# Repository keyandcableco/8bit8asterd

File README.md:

# 8b8 — 8-Bit 8asterd firmware

Arduino Leonardo driving three AY-3-8910A chips as a MIDI synth.

## Layout

- `8b8_firmware.ino` — the firmware
- `generate.py` — **single source of truth** for controllable parameters
- `parameters.h` — GENERATED. Do not edit by hand.
- `index.html` — GENERATED. Web Serial control panel (Chrome/Edge only).

## Workflow

Edit `PARAMS` / `PRESETS` in `generate.py`, then:

    python3 generate.py
    arduino-cli compile --fqbn arduino:avr:leonardo .
    arduino-cli upload -p /dev/ttyACM0 --fqbn arduino:avr:leonardo .

`generate.py` hashes the parameter definition into a layout-version byte.
When that byte changes the firmware ignores any saved EEPROM bank and boots
on defaults, so stale saves can never be misread as the new layout.

Open `index.html` directly in Chrome/Edge to control the unit. Close the tab
before flashing or the upload will fail on a busy serial port.

## Constraints

Leonardo (ATmega32u4): 28,672 bytes flash, 2,560 bytes RAM. RAM is the tight
one — keep constant tables in PROGMEM and read them with `pgm_read_*`.

Struct definitions must stay above the first function definition in the
.ino: the Arduino preprocessor inserts generated prototypes there, and a
type declared later breaks the build.

## License

Copyright © 2026 Greg Miller / The Key & Cable Company.

The firmware, browser emulator and tools are licensed under the [GNU General Public License v3.0](LICENSE). You can use, study, share and modify it. If you distribute it or a modified version, you have to make the source available under the same licence.

The hardware design files (the v2 board in `hardware/` on the `v2/rp2040` branch, and front-panel artwork) are licensed under the [CERN Open Hardware Licence Version 2 – Strongly Reciprocal (CERN-OHL-S-2.0)](LICENSE-HARDWARE). You can make, modify, sell and share hardware from them. If you share a modified design, or ship hardware made from one, you have to publish your design files under the same licence.

Source location: <https://github.com/keyandcableco/8bit8asterd>

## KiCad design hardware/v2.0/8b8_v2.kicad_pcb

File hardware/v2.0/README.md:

# 8b8 hardware v2.0

RP2040 board for three YM2149 / AY-3-8910 sound chips, with eight analog
and eight switch inputs on terminal blocks. Everything except the sound chips
and the through-hole connectors is SMD with an LCSC part number, so JLC can
assemble it.

| File | What it is |
|---|---|
| `8b8_v2.kicad_pro`, `.kicad_sch`, `.kicad_pcb` | KiCad 9 project |
| `tools/design.py` | **The netlist, as data.** Every part, footprint, LCSC number and net. |
| `tools/gen_sch.py` | Writes the schematic from `design.py` |
| `tools/gen_pcb.py` | Writes the unrouted board: placement, outline, planes, silkscreen |
| `tools/route.py` | Autoroutes with Freerouting, then adds the copper pours |
| `tools/fixroute.py` | Small A* router for connections the autorouter left open |
| `tools/stitch.py` | Ground vias: beside stranded pads, a 4 mm grid, and inside walled-in pockets |
| `tools/cleanup.py` | Removes dangling track leftovers |
| `tools/check_netlist.py` | Checks that the schematic KiCad reads back matches `design.py` |
| `tools/check_pcb.py` | Checks every pad's net against the schematic, then runs DRC |
| `tools/fab.py` | Writes the JLC package into `fab/` |
| `fab/` | Gerbers (zip), BOM, CPL, and the list of through-hole parts |
| `renders/` | 3D views of the board |

## Status

Checked on the board as committed:

- **Schematic:** KiCad reads back the same 111 nets as `design.py`, with 0 mismatches.
  ERC shows 8 warnings, all one intended thing: the three chips' analog outputs
  are summed, as on v1.0. It's downgraded from error to warning in the project file.
- **Board:** 110 x 90 mm, 4 layers. **DRC: 0 errors, 0 unconnected, 0 schematic
  parity issues.** Every pad carries the right net. 6 cosmetic silkscreen
  warnings remain (a few labels touching vias); JLC clips silk off copper.
- **Stackup:** F.Cu signals, In1 solid GND, In2 signals plus +5V / +3V3 pours,
  B.Cu signals plus GND pour, ~350 stitching vias.
- **Rules:** 0.2 mm tracks, 0.15 mm clearance, 0.25 mm power, 0.6 / 0.3 mm vias.
  All standard JLC 4-layer capability.

### Before ordering

1. **Open it in KiCad and look.** It's autorouted. It's electrically complete
   and DRC-clean, but nobody has eyeballed it yet. Check the RP2040 and crystal
   area in particular, and tidy anything that looks odd.
2. **Check part rotations in JLC's CPL preview.** KiCad and JLC disagree on the
   zero rotation of some footprints (SOT-23, SOIC, the USB-C). JLC shows a
   preview after upload. Rotate any part whose pin 1 sits in the wrong corner.
3. **Through-hole parts** (sockets, terminal blocks) are in `fab/hand_solder.txt`.
   Add them as JLC through-hole assembly, or solder them yourself.
4. **Extended parts:** most ICs are JLC "Extended" library parts, so expect the
   per-part setup fee on top of the parts cost.

## Rebuilding

```bash
cd hardware/v2.0/tools
python3 gen_sch.py && python3 check_netlist.py
/usr/bin/python3 gen_pcb.py                        # needs KiCad's pcbnew module
DISPLAY=:0 /usr/bin/python3 route.py /path/to/freerouting-1.9.0.jar 15
DISPLAY=:0 /usr/bin/python3 route.py /path/to/freerouting-1.9.0.jar 8   # second pass
/usr/bin/python3 fixroute.py && /usr/bin/python3 stitch.py && /usr/bin/python3 stitch.py --islands
/usr/bin/python3 cleanup.py && /usr/bin/python3 check_pcb.py
/usr/bin/python3 fab.py
```

Freerouting 1.9 needs a display; it shows a window while it works. Autorouting
isn't deterministic, so a rebuild won't produce exactly this board. The last
few connections on this one were finished with a rip-up and reroute around
three debounce caps.

`gen_pcb.py` overwrites the board. **Now that it's routed, edit the layout by
hand in KiCad** and use *Update PCB from Schematic* for any circuit change. The
footprints are linked to the schematic symbols, so that works.

## What changed from v1

| | v1.0 (Pro Micro) | v2.0 |
|---|---|---|
| MCU | Pro Micro module on headers (ATmega32U4) | RP2040 on the board, 4 MB QSPI flash, 12 MHz crystal |
| Programming | Arduino bootloader | Hold BOOT, plug in USB, copy a `.uf2`. No programmer needed. |
| Logic to the chips | 5V straight from the 32U4 | Two 74HCT245 buffers (3.3V in, 5V out) |
| Warp Zone bends | A, B, X, Y (data bits DA1, DA0, DA5, DA4) on J3 | **Removed.** The firmware's Warp Zone does this safely. |
| CLK / RESET on J3 | `/SEL` (the half-clock bend) and `/RESET` | **Removed.** Clock Warp does the clock; reset is internal. |
| Inputs | none | 8 analog (74HC4051 to ADC0), 8 switch (74HC165) |
| Power | USB via Pro Micro | USB-C, 0.75 A polyfuse, AP2112K 3.3 V regulator |
| Audio out | 1k / 47n / 1u / 100k network | Same network, same values |
| MIDI in | 6N137, 220R, 1N4148 | Same circuit; output pulled up to 3.3 V |

## RP2040 pin map (for the firmware port)

| GPIO | Signal | Notes |
|---|---|---|
| 0-7 | DA0-DA7 | Data bus via U5. One masked write: `gpio_put_masked(0xFF, b)` |
| 8, 9 | BDIR_A, BC2_A | Chip A control via U6 |
| 10, 11 | BDIR_B, BC2_B | Chip B |
| 12, 13 | BDIR_C, BC2_C | Chip C |
| 14 | /RESET | All three chips. Pulled low until firmware drives it. |
| 15 | LED MIDI | Active high |
| 16 | spare | Test pad (UART0 TX, so a future MIDI out) |
| 17 | MIDI RX | UART0 RX, 31250 baud |
| 18, 19, 20 | MUX S0, S1, S2 | 74HC4051 channel select |
| 21 | CLOCK | GPOUT0. `clk_sys / 125` at 125 MHz gives exactly 1 MHz. Through U6, then 75R, then pin 22 of each chip. |
| 22, 23, 24 | SR /PL, CP, Q7 | 74HC165 |
| 25 | LED STATUS | Active high |
| 26 | MUX Z | ADC0 |
| 27, 28, 29 | spare | Test pads; ADC1-3 |

BC1 is grounded on every chip, the same reduced scheme as v1, so the
register-write sequence is unchanged.

Inside U5 and U6, channel *k* carries bit 7−*k*. That makes the bus run
straight from the RP2040 to the chips without crossing. It doesn't affect the
firmware: GPIO*n* still drives DA*n*.

### Reading the inputs

- **Analog:** set S2..S0 to the channel, wait about 10 µs, then read ADC0.
  Each input has 1k series and 10nF to ground. Pot ends go to the terminal's
  3V3 and GND pins, so the reading is ratiometric.
- **Switches:** pulse /PL low to latch, then clock out 8 bits on CP and read Q7.
  D0 (switch 1) comes out first. Inputs are active low: closed = 0. Each has
  a 10k pull-up and 1k/100nF debounce.

## Open questions

1. **v1.0 C2 is labelled "47uF" but drawn as a 5 mm disc ceramic.** v2.0 uses
   47 nF (3.4 kHz low-pass with the 1k). If your built v1 boards really have
   47 µF there, change it in `design.py`.
2. **v1.0 MIDI terminal labels.** v1's J3 labels the opto-cathode side "MIDI 4"
   and the 220R side "MIDI 5". The MIDI spec has DIN pin 4 on the resistor side,
   so v2.0 labels it that way. The circuit is identical; only the silkscreen
   differs.
3. **/A9, A8 and /SEL are left open, as on v1.0.** The chips pull them to the
   normal state. Tie them explicitly if you prefer.

## License

Copyright © 2026 Greg Miller / The Key & Cable Company.

The v2 hardware design files are licensed under the [CERN Open Hardware Licence Version 2 – Strongly Reciprocal (CERN-OHL-S-2.0)](../../LICENSE-HARDWARE). You can make, modify, sell and share hardware from them. If you share a modified design, or ship hardware made from one, you have to publish your design files under the same licence. The firmware is GPL-3.0 (see [LICENSE](../../LICENSE)).

Source location: <https://github.com/keyandcableco/8bit8asterd>

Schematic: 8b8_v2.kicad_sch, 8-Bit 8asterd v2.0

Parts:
C1, C2, C3: 10uF; C_0603_1608Metric; LCSC C96446
C4, C16, C17: 1uF; C_0402_1005Metric; LCSC C52923
C5: 10uF; C_0603_1608Metric; LCSC C19702
C6, C7, C8, C9, C10, C11, C12, C13, C14, C15, C20, C21, C22, C23, C24, C25, C28, C29, C38, C39, C40, C41, C42, C43, C44, C45, C46: 100nF; C_0402_1005Metric; LCSC C1525
C18, C19: 15pF; C_0402_1005Metric; LCSC C1548
C26: 47nF; C_0402_1005Metric; LCSC C272875
C27: 1uF; C_0603_1608Metric; LCSC C106248
C30, C31, C32, C33, C34, C35, C36, C37: 10nF; C_0402_1005Metric; LCSC C15195
D1: PWR; LED_0603_1608Metric; LCSC C12624
D2: MIDI; LED_0603_1608Metric; LCSC C12624
D3: STATUS; LED_0603_1608Metric; LCSC C2286
D4: 1N4148W; D_SOD-123; LCSC C81598
F1: 0.75A; Fuse_1206_3216Metric; LCSC C70078
H1, H2, H3, H4: M3; MountingHole_3.2mm_M3
J1: USB-C; USB_C_Receptacle_HRO_TYPE-C-31-M-12; LCSC C165948
J2: AUDIO OUT; PhoenixContact_MC_1,5_2-G-3.5_1x02_P3.50mm_Horizontal; LCSC C395830
J3: MIDI IN; PhoenixContact_MC_1,5_2-G-3.5_1x02_P3.50mm_Horizontal; LCSC C395830
J4: ANALOG IN; PhoenixContact_MC_1,5_10-G-3.5_1x10_P3.50mm_Horizontal; LCSC C430562
J5: SWITCH IN; PhoenixContact_MC_1,5_10-G-3.5_1x10_P3.50mm_Horizontal; LCSC C430562
R1, R2: 5.1k; R_0402_1005Metric; LCSC C25905
R3, R4, R5, R8, R9, R19, R23, R24, R25, R26, R27, R28, R29, R30, R31, R33, R35, R37, R39, R41, R43, R45: 1k; R_0402_1005Metric; LCSC C11702
R6, R7: 27; R_0402_1005Metric; LCSC C25156
R10, R11, R12, R13, R14, R15, R16, R17, R20: 100k; R_0402_1005Metric; LCSC C25741
R18: 75; R_0402_1005Metric; LCSC C25133
R21: 220; R_0402_1005Metric; LCSC C25091
R22, R32, R34, R36, R38, R40, R42, R44, R46: 10k; R_0402_1005Metric; LCSC C25744
SW1: BOOT; SW_Push_1P1T_NO_CK_KMR2; LCSC C318884
SW2: RESET; SW_Push_1P1T_NO_CK_KMR2; LCSC C318884
TP_3V3: TP_3V3; TestPoint_Pad_D1.0mm
TP_5V: TP_5V; TestPoint_Pad_D1.0mm
TP_GND: TP_GND; TestPoint_Pad_D1.0mm
TP_GP16: TP_GP16; TestPoint_Pad_D1.0mm
TP_GP27: TP_GP27; TestPoint_Pad_D1.0mm
TP_GP28: TP_GP28; TestPoint_Pad_D1.0mm
TP_GP29: TP_GP29; TestPoint_Pad_D1.0mm
TP_SWCLK: TP_SWCLK; TestPoint_Pad_D1.0mm
TP_SWD: TP_SWD; TestPoint_Pad_D1.0mm
U1: AP2112K-3.3; SOT-23-5; LCSC C51118
U2: RP2040; QFN-56-1EP_7x7mm_P0.4mm_EP3.2x3.2mm; LCSC C2040
U3: W25Q32JVSSIQ; SOIC-8_5.3x5.3mm_P1.27mm; LCSC C179173
U4: USBLC6-2SC6; SOT-23-6; LCSC C7519
U5, U6: 74HCT245; SOIC-20W_7.5x12.8mm_P1.27mm; LCSC C5979
U7, U8, U9: YM2149 / AY-3-8910; DIP-40_W15.24mm_Socket; LCSC C2332
U10: 6N137S; SMDIP-8_W9.53mm; LCSC C16496
U11: 74HC4051; SOIC-16_3.9x9.9mm_P1.27mm; LCSC C9386
U12: 74HC165; SOIC-16_3.9x9.9mm_P1.27mm; LCSC C5613
Y1: 12MHz; Crystal_SMD_3225-4Pin_3.2x2.5mm; LCSC C9002

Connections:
+1V1: C14.1, C15.1, C17.1, U2.23 (DVDD), U2.45 (VREG_VOUT), U2.50 (DVDD)
+3V3: C5.1, C6.1, C7.1, C8.1, C9.1, C10.1, C11.1, C12.1, C13.1, C16.1, C20.1, C29.1, C38.1, J4.9, J5.10, R22.2, R32.2, R34.2, R36.2, R38.2, R40.2, R42.2, R44.2, R46.2, TP_3V3.1, U1.5 (VOUT), U2.1 (IOVDD), U2.10 (IOVDD), U2.22 (IOVDD), U2.33 (IOVDD), U2.42 (IOVDD), U2.43 (ADC_AVDD), U2.44 (VREG_VIN), U2.48 (USB_VDD), U2.49 (IOVDD), U3.8 (VCC), U11.16 (VCC), U12.16 (VCC)
+5V: C1.1, C2.1, C3.1, C4.1, C21.1, C22.1, C23.1, C24.1, C25.1, C28.1, F1.2, R3.1, TP_5V.1, U1.1 (VIN), U1.3 (EN), U5.1 (A->B), U5.20 (VCC), U6.1 (A->B), U6.20 (VCC), U7.40 (VCC), U8.40 (VCC), U9.40 (VCC), U10.7 (EN), U10.8 (VCC)
/AUDIO: C26.1, C27.1, R19.1, U7.3 (A), U7.4 (B), U7.38 (C), U8.3 (A), U8.4 (B), U8.38 (C), U9.3 (A), U9.4 (B), U9.38 (C)
/AUDIO_OUT: C27.2, J2.1, R20.1
/AY_CLK: R18.2, U7.22 (CLOCK), U8.22 (CLOCK), U9.22 (CLOCK)
/AY_RESET: U6.17 (B1), U7.23 (~RESET), U8.23 (~RESET), U9.23 (~RESET)
/BC2_A: U6.12 (B6), U7.28 (BC2)
/BC2_A_MCU: R11.1, U2.12 (GPIO9), U6.8 (A6)
/BC2_B: U6.14 (B4), U8.28 (BC2)
/BC2_B_MCU: R13.1, U2.14 (GPIO11), U6.6 (A4)
/BC2_C: U6.16 (B2), U9.28 (BC2)
/BC2_C_MCU: R15.1, U2.16 (GPIO13), U6.4 (A2)
/BDIR_A: U6.11 (B7), U7.27 (BDIR)
/BDIR_A_MCU: R10.1, U2.11 (GPIO8), U6.9 (A7)
/BDIR_B: U6.13 (B5), U8.27 (BDIR)
/BDIR_B_MCU: R12.1, U2.13 (GPIO10), U6.7 (A5)
/BDIR_C: U6.15 (B3), U9.27 (BDIR)
/BDIR_C_MCU: R14.1, U2.15 (GPIO12), U6.5 (A3)
/BOOTSEL: R5.2, SW1.1
/CC1: J1.A5 (CC1), R1.1
/CC2: J1.B5 (CC2), R2.1
/CLK_BUF: R18.1, U6.18 (B0)
/CLK_MCU: R17.1, U2.32 (GPIO21), U6.2 (A0)
/D0_MCU: U2.2 (GPIO0), U5.9 (A7)
/D1_MCU: U2.3 (GPIO1), U5.8 (A6)
/D2_MCU: U2.4 (GPIO2), U5.7 (A5)
/D3_MCU: U2.5 (GPIO3), U5.6 (A4)
/D4_MCU: U2.6 (GPIO4), U5.5 (A3)
/D5_MCU: U2.7 (GPIO5), U5.4 (A2)
/D6_MCU: U2.8 (GPIO6), U5.3 (A1)
/D7_MCU: U2.9 (GPIO7), U5.2 (A0)
/DA0: U5.11 (B7), U7.37 (DA0), U8.37 (DA0), U9.37 (DA0)
/DA1: U5.12 (B6), U7.36 (DA1), U8.36 (DA1), U9.36 (DA1)
/DA2: U5.13 (B5), U7.35 (DA2), U8.35 (DA2), U9.35 (DA2)
/DA3: U5.14 (B4), U7.34 (DA3), U8.34 (DA3), U9.34 (DA3)
/DA4: U5.15 (B3), U7.33 (DA4), U8.33 (DA4), U9.33 (DA4)
/DA5: U5.16 (B2), U7.32 (DA5), U8.32 (DA5), U9.32 (DA5)
/DA6: U5.17 (B1), U7.31 (DA6), U8.31 (DA6), U9.31 (DA6)
/DA7: U5.18 (B0), U7.30 (DA7), U8.30 (DA7), U9.30 (DA7)
/GP16: TP_GP16.1, U2.27 (GPIO16)
/GP27: TP_GP27.1, U2.39 (GPIO27/ADC1)
/GP28: TP_GP28.1, U2.40 (GPIO28/ADC2)
/GP29: TP_GP29.1, U2.41 (GPIO29/ADC3)
/IN_A1: J4.1, R23.1
/IN_A2: J4.2, R24.1
/IN_A3: J4.3, R25.1
/IN_A4: J4.4, R26.1
/IN_A5: J4.5, R27.1
/IN_A6: J4.6, R28.1
/IN_A7: J4.7, R29.1
/IN_A8: J4.8, R30.1
/IN_D1: J5.1, R31.1
/IN_D2: J5.2, R33.1
/IN_D3: J5.3, R35.1
/IN_D4: J5.4, R37.1
/IN_D5: J5.5, R39.1
/IN_D6: J5.6, R41.1
/IN_D7: J5.7, R43.1
/IN_D8: J5.8, R45.1
/LED_MIDI_A: D2.2 (A), R8.2
/LED_MIDI_MCU: R8.1, U2.18 (GPIO15)
/LED_PWR_A: D1.2 (A), R3.2
/LED_STAT_A: D3.2 (A), R9.2
/LED_STAT_MCU: R9.1, U2.37 (GPIO25)
/MIDI_4: J3.2, R21.1
/MIDI_5: D4.2 (A), J3.1, U10.3 (C)
/MIDI_RX: R22.1, U2.28 (GPIO17), U10.6 (VO)
/MUX_S0: U2.29 (GPIO18), U11.11 (S0)
/MUX_S1: U2.30 (GPIO19), U11.10 (S1)
/MUX_S2: U2.31 (GPIO20), U11.9 (S2)
/MUX_Y0: C30.1, R23.2, U11.13 (A0)
/MUX_Y1: C31.1, R24.2, U11.14 (A1)
/MUX_Y2: C32.1, R25.2, U11.15 (A2)
/MUX_Y3: C33.1, R26.2, U11.12 (A3)
/MUX_Y4: C34.1, R27.2, U11.1 (A4)
/MUX_Y5: C35.1, R28.2, U11.5 (A5)
/MUX_Y6: C36.1, R29.2, U11.2 (A6)
/MUX_Y7: C37.1, R30.2, U11.4 (A7)
/MUX_Z: U2.38 (GPIO26/ADC0), U11.3 (A)
/OPTO_A: D4.1 (K), R21.2, U10.2 (A)
/QSPI_SCLK: U2.52 (QSPI_SCLK), U3.6 (CLK)
/QSPI_SD0: U2.53 (QSPI_SD0), U3.5 (DI/IO_{0})
/QSPI_SD1: U2.55 (QSPI_SD1), U3.2 (DO/IO_{1})
/QSPI_SD2: U2.54 (QSPI_SD2), U3.3 (~WP/IO_{2})
/QSPI_SD3: U2.51 (QSPI_SD3), U3.7 (~HOLD/~RESET/IO_{3})
/QSPI_SS: R5.1, U2.56 (~QSPI_SS), U3.1 (~CS)
/RESET_MCU: R16.1, U2.17 (GPIO14), U6.3 (A1)
/RUN: SW2.1, U2.26 (RUN)
/SR_CP: U2.35 (GPIO23), U12.2 (CP)
/SR_PL: U2.34 (GPIO22), U12.1 (~PL)
/SR_Q7: U2.36 (GPIO24), U12.9 (Q7)
/SWCLK: TP_SWCLK.1, U2.24 (SWCLK)
/SWD: TP_SWD.1, U2.25 (SWDIO)
/SW_D0: C39.1, R31.2, R32.1, U12.11 (D0)
/SW_D1: C40.1, R33.2, R34.1, U12.12 (D1)
/SW_D2: C41.1, R35.2, R36.1, U12.13 (D2)
/SW_D3: C42.1, R37.2, R38.1, U12.14 (D3)
/SW_D4: C43.1, R39.2, R40.1, U12.3 (D4)
/SW_D5: C44.1, R41.2, R42.1, U12.4 (D5)
/SW_D6: C45.1, R43.2, R44.1, U12.5 (D6)
/SW_D7: C46.1, R45.2, R46.1, U12.6 (D7)
/USB_DM: R7.2, U2.46 (USB_DM)
/USB_DM_C: J1.A7 (D-), J1.B7 (D-), R7.1, U4.3 (I/O2), U4.4 (I/O2)
/USB_DP: R6.2, U2.47 (USB_DP)
/USB_DP_C: J1.A6 (D+), J1.B6 (D+), R6.1, U4.1 (I/O1), U4.6 (I/O1)
/VBUS: F1.1, J1.A4 (VBUS), J1.A9 (VBUS), J1.B4 (VBUS), J1.B9 (VBUS), U4.5 (VBUS)
/XIN: C18.1, U2.20 (XIN), Y1.1
/XOUT_MCU: R4.1, U2.21 (XOUT)
/XOUT_X: C19.1, R4.2, Y1.3
GND: C1.2, C2.2, C3.2, C4.2, C5.2, C6.2, C7.2, C8.2, C9.2, C10.2, C11.2, C12.2, C13.2, C14.2, C15.2, C16.2, C17.2, C18.2, C19.2, C20.2, C21.2, C22.2, C23.2, C24.2, C25.2, C26.2, C28.2, C29.2, C30.2, C31.2, C32.2, C33.2, C34.2, C35.2, C36.2, C37.2, C38.2, C39.2, C40.2, C41.2, C42.2, C43.2, C44.2, C45.2, C46.2, D1.1 (K), D2.1 (K), D3.1 (K), J1.A1 (GND), J1.A12 (GND), J1.B1 (GND), J1.B12 (GND), J1.S1 (SHIELD), J2.2, J4.10, J5.9, R1.2, R2.2, R10.2, R11.2, R12.2, R13.2, R14.2, R15.2, R16.2, R17.2, R19.2, R20.2, SW1.2, SW2.2, TP_GND.1, U1.2 (GND), U2.19 (TESTEN), U2.57 (GND), U3.4 (GND), U4.2 (GND), U5.10 (GND), U5.19 (CE), U6.10 (GND), U6.19 (CE), U7.1 (VSS), U7.29 (BC1), U8.1 (VSS), U8.29 (BC1), U9.1 (VSS), U9.29 (BC1), U10.5 (GND), U11.6 (~E), U11.7 (VEE), U11.8 (GND), U12.8 (GND), U12.10 (DS), U12.15 (~CE), Y1.2 (G), Y1.4 (G)

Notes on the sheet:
POWER: USB-C -> fuse -> 5V -> 3.3V
RP2040 CORE
3.3V -> 5V LEVEL BUFFERS
THREE YM2149 / AY-3-8910 SOUND CHIPS
AUDIO OUT (same network as v1.0)
MIDI IN
INPUTS: 8 analog (74HC4051) + 8 digital (74HC165)
MECHANICAL

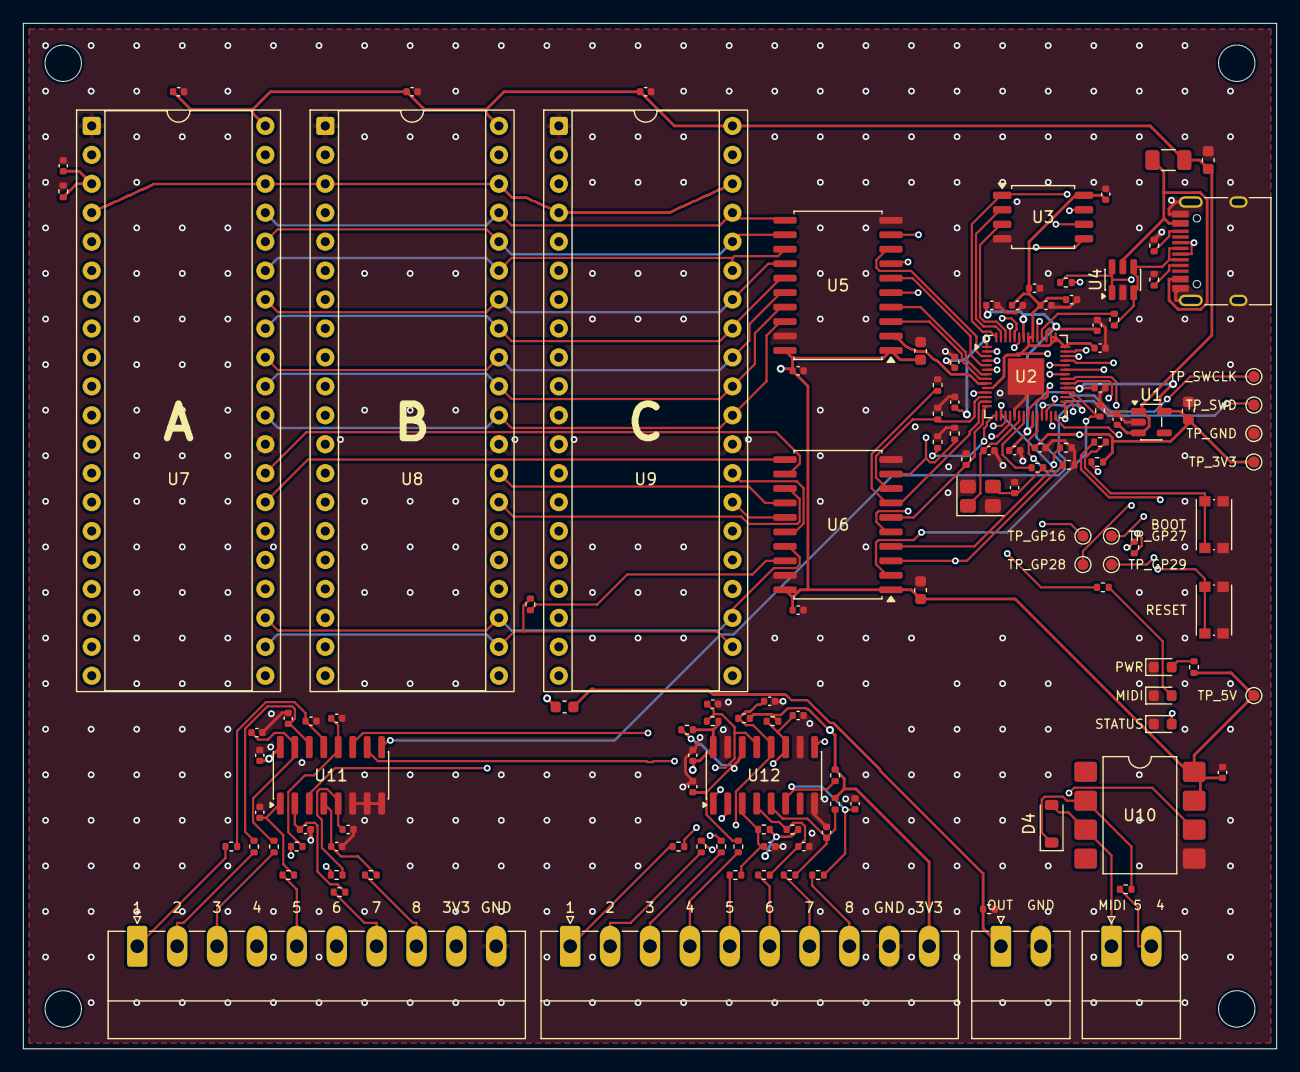
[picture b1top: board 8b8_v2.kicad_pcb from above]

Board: 4 copper layers, 110.0 x 90.0 mm, 130 parts (0 on the bottom side), 111 nets.

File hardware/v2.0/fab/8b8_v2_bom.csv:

Comment,Designator,Footprint,LCSC Part #
10uF,"C1,C2,C3",C_0603_1608Metric,C96446
15pF,"C18,C19",C_0402_1005Metric,C1548
47nF,C26,C_0402_1005Metric,C272875
1uF,C27,C_0603_1608Metric,C106248
10nF,"C30,C31,C32,C33,C34,C35,C36,C37",C_0402_1005Metric,C15195
1uF,"C4,C16,C17",C_0402_1005Metric,C52923
10uF,C5,C_0603_1608Metric,C19702
100nF,"C6,C7,C8,C9,C10,C11,C12,C13,C14,C15,C20,C21,C22,C23,C24,C25,C28,C29,C38,C39,C40,C41,C42,C43,C44,C45,C46",C_0402_1005Metric,C1525
PWR,D1,LED_0603_1608Metric,C12624
MIDI,D2,LED_0603_1608Metric,C12624
STATUS,D3,LED_0603_1608Metric,C2286
1N4148W,D4,D_SOD-123,C81598
0.75A,F1,Fuse_1206_3216Metric,C70078
USB-C,J1,USB_C_Receptacle_HRO_TYPE-C-31-M-12,C165948
5.1k,"R1,R2",R_0402_1005Metric,C25905
100k,"R10,R11,R12,R13,R14,R15,R16,R17,R20",R_0402_1005Metric,C25741
75,R18,R_0402_1005Metric,C25133
220,R21,R_0402_1005Metric,C25091
10k,"R22,R32,R34,R36,R38,R40,R42,R44,R46",R_0402_1005Metric,C25744
1k,"R3,R4,R5,R8,R9,R19,R23,R24,R25,R26,R27,R28,R29,R30,R31,R33,R35,R37,R39,R41,R43,R45",R_0402_1005Metric,C11702
27,"R6,R7",R_0402_1005Metric,C25156
BOOT,SW1,SW_Push_1P1T_NO_CK_KMR2,C318884
RESET,SW2,SW_Push_1P1T_NO_CK_KMR2,C318884
AP2112K-3.3,U1,SOT-23-5,C51118
6N137S,U10,SMDIP-8_W9.53mm,C16496
74HC4051,U11,SOIC-16_3.9x9.9mm_P1.27mm,C9386
74HC165,U12,SOIC-16_3.9x9.9mm_P1.27mm,C5613
RP2040,U2,QFN-56-1EP_7x7mm_P0.4mm_EP3.2x3.2mm,C2040
W25Q32JVSSIQ,U3,SOIC-8_5.3x5.3mm_P1.27mm,C179173
USBLC6-2SC6,U4,SOT-23-6,C7519
74HCT245,"U5,U6",SOIC-20W_7.5x12.8mm_P1.27mm,C5979
12MHz,Y1,Crystal_SMD_3225-4Pin_3.2x2.5mm,C9002

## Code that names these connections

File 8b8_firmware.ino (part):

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static const uint8_t dbus[8] PROGMEM = { 2, 3, 4, 5, 6, 7, 8, 10 };

static const ushort
  BC2_A = 14,
  BDIR_A = 16,
  BC2_B = A1,
  BDIR_B = A0,
  BC2_C = A3,
  BDIR_C = A2,
  nRESET = 15,
  clkOUT = 9;

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    dbusPins[i].mask = digitalPinToBitMask(pin);
  }

  const ushort bdirPins[3] = { BDIR_A, BDIR_B, BDIR_C };
  const ushort bc2Pins[3]  = { BC2_A,  BC2_B,  BC2_C  };

  for (uint8_t c = 0; c < 3; c++) {
    chipCtl[c].bdir.port = portOutputRegister(digitalPinToPort(bdirPins[c]));
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  digitalWrite(clkOUT, LOW);
  clockSetup();

  pinMode(BC2_A, OUTPUT);
  digitalWrite(BC2_A, LOW); // BC2 low
  pinMode(BDIR_A, OUTPUT);
  digitalWrite(BDIR_A, LOW); // BDIR low

  pinMode(BC2_B, OUTPUT);
  digitalWrite(BC2_B, LOW); // BC2 low
  pinMode(BDIR_B, OUTPUT);
  digitalWrite(BDIR_B, LOW); // BDIR low

  pinMode(BC2_C, OUTPUT);
  digitalWrite(BC2_C, LOW); // BC2 low
  pinMode(BDIR_C, OUTPUT);
  digitalWrite(BDIR_C, LOW); // BDIR low

  for (ushort i = 0; i < 8; i++) {
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
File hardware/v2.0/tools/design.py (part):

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R('1k', 'LED_MIDI_MCU', 'LED_MIDI_A', LC['r1k'], section=S)
add('D3', 'Device:LED', LED0603, 'STATUS', LC['led_r'], {'2': 'LED_STAT_A', '1': 'GND'}, section=S)
R('1k', 'LED_STAT_MCU', 'LED_STAT_A', LC['r1k'], section=S)
# test points: SWD, spare GPIOs, rails
for name, net in [('SWCLK', 'SWCLK'), ('SWD', 'SWD'), ('GP16', 'GP16'), ('GP27', 'GP27'),
                  ('GP28', 'GP28'), ('GP29', 'GP29'), ('3V3', '+3V3'), ('5V', '+5V'),
                  ('GND', 'GND')]:
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# ===========================================================================
S = 'midi'
add('J3', 'Connector:Screw_Terminal_01x02', FP_TERM2, 'MIDI IN', LC['term2'],
    {'1': 'MIDI_5', '2': 'MIDI_4'}, note='DIN pin 5 / DIN pin 4', section=S)
R('220', 'MIDI_4', 'OPTO_A', LC['r220'], section=S)
add('U10', 'Isolator:6N137', 'Package_DIP:SMDIP-8_W9.53mm', '6N137S', LC['opto'],
    {'1': 'NC_O1', '2': 'OPTO_A', '3': 'MIDI_5', '4': 'NC_O4', '5': 'GND', '6': 'MIDI_RX_OC',
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    note='reverse-polarity protection across the opto LED', section=S)
R('10k', 'MIDI_RX_OC', '+3V3', LC['r10k'], section=S)
bypass('+5V', 1, S)
# MIDI_RX_OC is the open-collector node; MIDI_RX is the same signal at the MCU pin.
# They are one net: rename so the schematic shows a single net.
PARTS['U10']['pins']['6'] = 'MIDI_RX'
for ref in list(PARTS):
    for k, v in PARTS[ref]['pins'].items():
        if v == 'MIDI_RX_OC':
            PARTS[ref]['pins'][k] = 'MIDI_RX'

# ===========================================================================
# INPUTS: 8 analog (74HC4051) and 8 digital (74HC165) on pluggable terminals
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

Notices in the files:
8b8_firmware.ino:
Copyright (C) 2026 Greg Miller, The Key & Cable Company
under the terms of the GNU General Public License as published by the Free
Public License along with this program. If not, see
<https://www.gnu.org/licenses/>.
